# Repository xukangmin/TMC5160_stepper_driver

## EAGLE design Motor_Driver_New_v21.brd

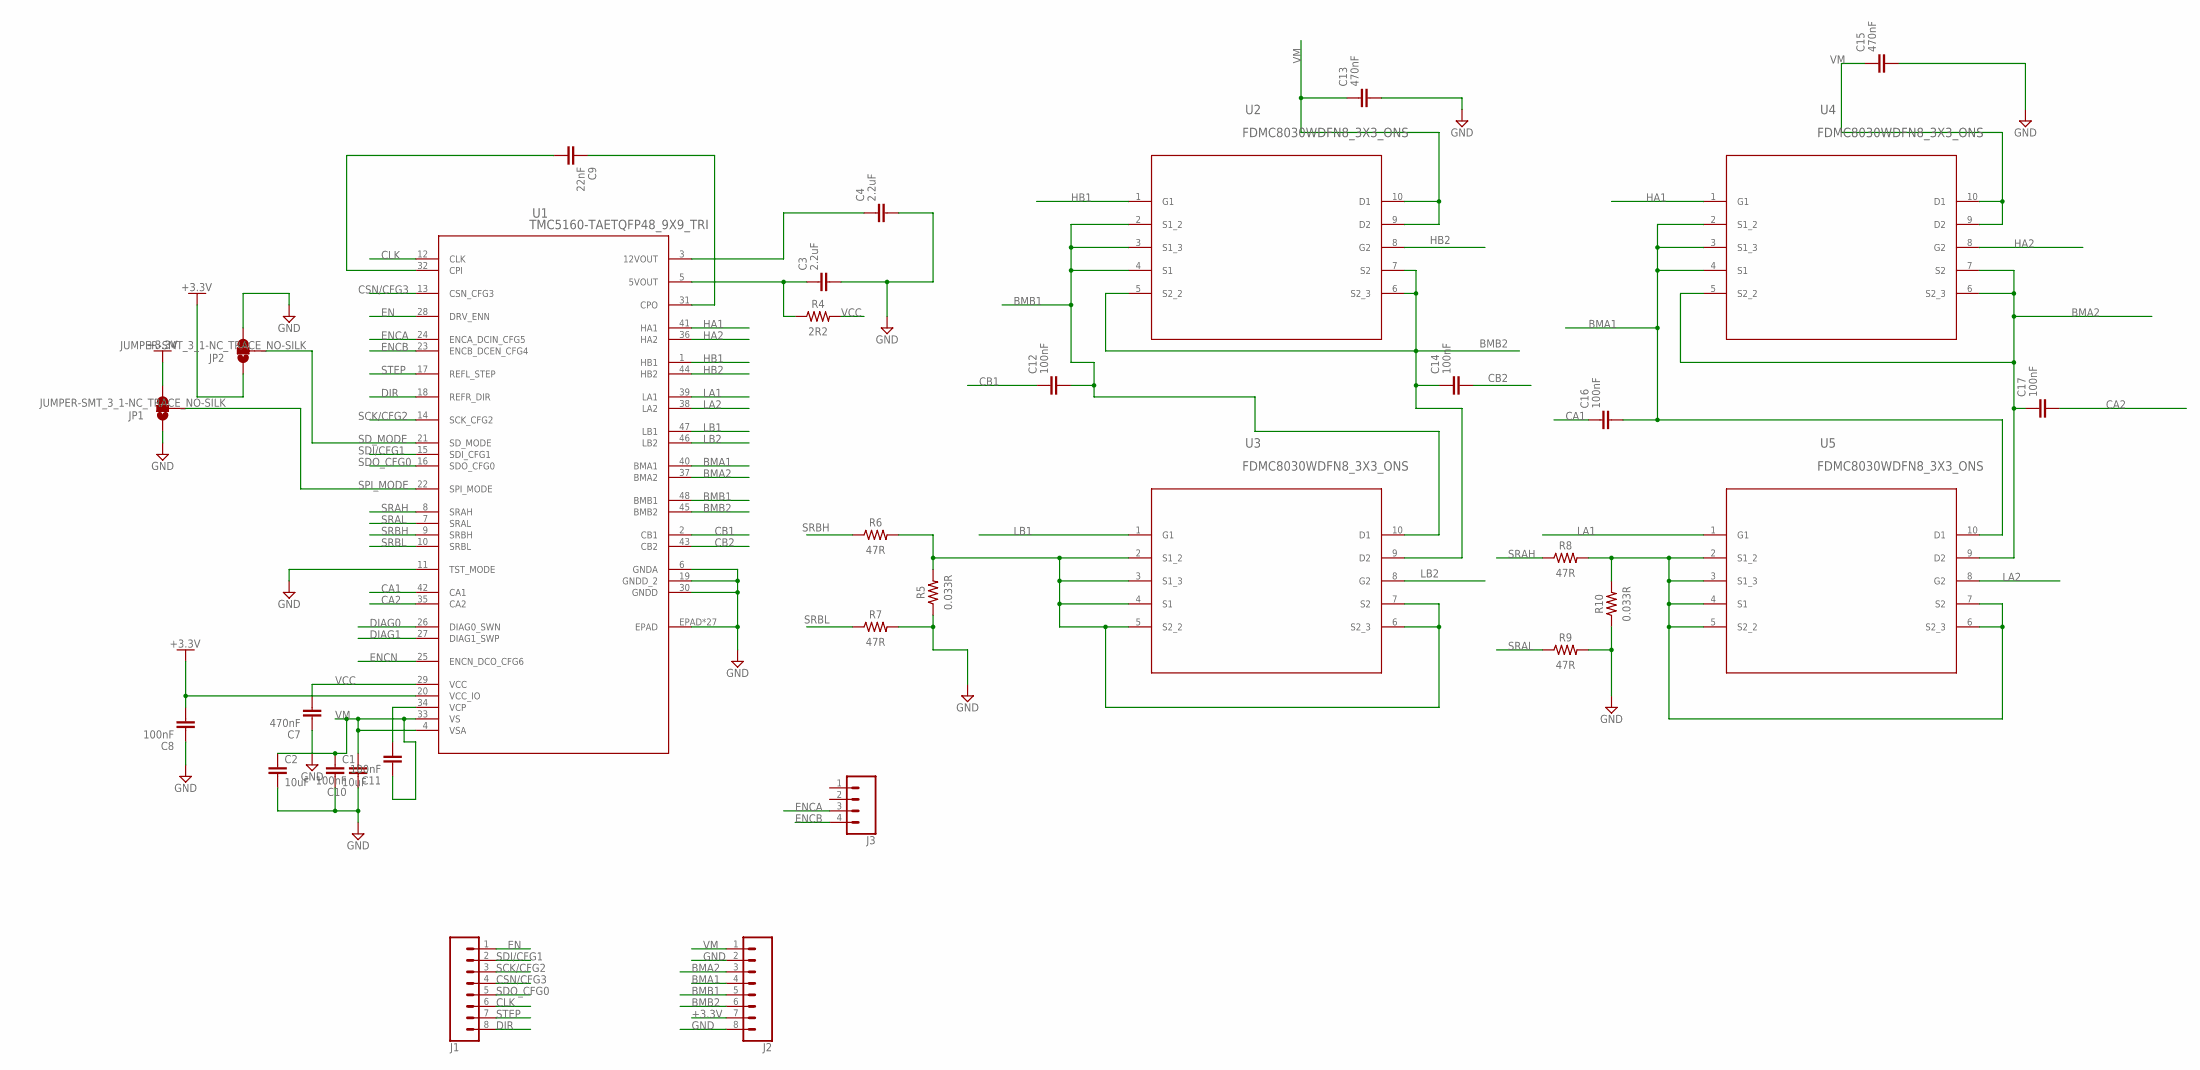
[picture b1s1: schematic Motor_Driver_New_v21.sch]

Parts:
C1, C2: 10uF; 0805
C3, C4: 2.2uF; CAPC1005X60
C7, C13, C15: 470nF; CAPC1005X60
C8, C10, C11, C12, C14, C16, C17: 100nF; CAPC1005X60
C9: 22nF; CAPC1005X60
J1, J2: CONN_08"; 1X08
J3: CONN_04PTH; 1X04
JP1, JP2: JUMPER-SMT_3_1-NC_TRACE_NO-SILK; SMT-JUMPER_3_1-NC_TRACE_NO-SILK
R4: 2R2; RESC1005X40
R5, R10: 0.033R; RESC3216X70
R6, R7, R8, R9: 47R; RESC1005X40
U1: TMC5160-TAETQFP48_9X9_TRI; ETQFP48_9X9_TRI
U2, U3, U4, U5: FDMC8030WDFN8_3X3_ONS; WDFN8_3X3_ONS

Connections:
+3.3V: C8.2, J2.7, JP1.3, JP2.1, U1.20 (VCC_IO)
BMA1: C16.2, J2.4, U1.40 (BMA1), U4.2 (S1_2), U4.3 (S1_3), U4.4 (S1), U5.10 (D1)
BMA2: C17.1, J2.3, U1.37 (BMA2), U4.5 (S2_2), U4.6 (S2_3), U4.7 (S2), U5.9 (D2)
BMB1: C12.2, J2.5, U1.48 (BMB1), U2.2 (S1_2), U2.3 (S1_3), U2.4 (S1), U3.10 (D1)
BMB2: C14.1, J2.6, U1.45 (BMB2), U2.5 (S2_2), U2.6 (S2_3), U2.7 (S2), U3.9 (D2)
CA1: C16.1, U1.42 (CA1)
CA2: C17.2, U1.35 (CA2)
CB1: C12.1, U1.2 (CB1)
CB2: C14.2, U1.43 (CB2)
CLK: J1.6, U1.12 (CLK)
CSN/CFG3: J1.4, U1.13 (CSN_CFG3)
DIAG0: U1.26 (DIAG0_SWN)
DIAG1: U1.27 (DIAG1_SWP)
DIR: J1.8, U1.18 (REFR_DIR)
EN: J1.1, U1.28 (DRV_ENN)
ENCA: J3.3, U1.24 (ENCA_DCIN_CFG5)
ENCB: J3.4, U1.23 (ENCB_DCEN_CFG4)
ENCN: U1.25 (ENCN_DCO_CFG6)
GND: C1.2, C2.2, C3.2, C4.2, C7.1, C8.1, C10.1, C13.2, C15.2, J2.2, J2.8, JP1.1, JP2.3, R5.1, R7.2, R9.2, R10.1, U1.6 (GNDA), U1.11 (TST_MODE), U1.19 (GNDD_2), U1.30 (GNDD), U1.EPAD, U1.EPAD1 (EPAD), U1.P$1 (EPAD), U1.P$2 (EPAD), U1.P$3 (EPAD), U1.P$4 (EPAD), U1.P$5 (EPAD), U1.P$6 (EPAD), U1.P$7 (EPAD), U1.P$8 (EPAD), U1.P$9 (EPAD), U1.P$10 (EPAD), U1.P$11 (EPAD), U1.P$12 (EPAD), U1.P$13 (EPAD), U1.P$14 (EPAD), U1.P$15 (EPAD), U1.P$16 (EPAD), U1.P$17 (EPAD), U1.P$18 (EPAD), U1.P$19 (EPAD), U1.P$20 (EPAD), U1.P$21 (EPAD), U1.P$22 (EPAD), U1.P$23 (EPAD), U1.P$24 (EPAD), U1.P$25 (EPAD)
HA1: U1.41 (HA1), U4.1 (G1)
HA2: U1.36 (HA2), U4.8 (G2)
HB1: U1.1 (HB1), U2.1 (G1)
HB2: U1.44 (HB2), U2.8 (G2)
LA1: U1.39 (LA1), U5.1 (G1)
LA2: U1.38 (LA2), U5.8 (G2)
LB1: U1.47 (LB1), U3.1 (G1)
LB2: U1.46 (LB2), U3.8 (G2)
unnamed: C3.1, R4.1, U1.5 (5VOUT)
unnamed: C4.1, U1.3 (12VOUT)
unnamed: C9.2, U1.32 (CPI)
unnamed: C9.1, U1.31 (CPO)
unnamed: C11.2, U1.34 (VCP)
SCK/CFG2: J1.3, U1.14 (SCK_CFG2)
SDI/CFG1: J1.2, U1.15 (SDI_CFG1)
SDO_CFG0: J1.5, U1.16 (SDO_CFG0)
SD_MODE: JP2.2, U1.21 (SD_MODE)
SPI_MODE: JP1.2, U1.22 (SPI_MODE)
SRAH: R8.1, U1.8 (SRAH)
SRAHL: R8.2, R10.2, U5.2 (S1_2), U5.3 (S1_3), U5.4 (S1), U5.5 (S2_2), U5.6 (S2_3), U5.7 (S2)
SRAL: R9.1, U1.7 (SRAL)
SRBH: R6.1, U1.9 (SRBH)
SRBHL: R5.2, R6.2, U3.2 (S1_2), U3.3 (S1_3), U3.4 (S1), U3.5 (S2_2), U3.6 (S2_3), U3.7 (S2)
SRBL: R7.1, U1.10 (SRBL)
STEP: J1.7, U1.17 (REFL_STEP)
VCC: C7.2, R4.2, U1.29 (VCC)
VM: C1.1, C2.1, C10.2, C11.1, C13.1, C15.1, J2.1, U1.4 (VSA), U1.33 (VS), U2.9 (D2), U2.10 (D1), U4.9 (D2), U4.10 (D1)

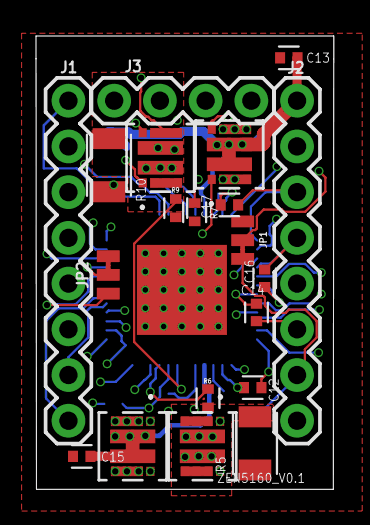
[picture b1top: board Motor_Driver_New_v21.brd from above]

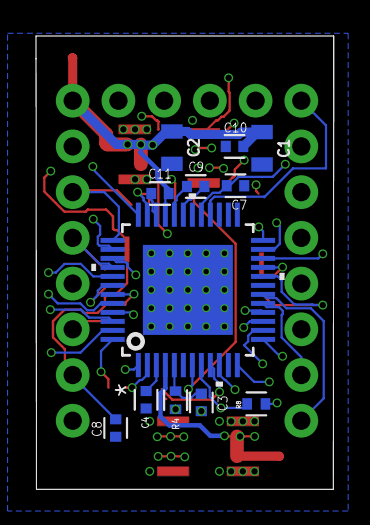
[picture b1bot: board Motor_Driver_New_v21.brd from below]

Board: 6 copper layers, 16.5 x 25.2 mm, 32 parts (12 on the bottom side), 43 nets.

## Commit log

2024-08-11 init

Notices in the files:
parts and their libraries:
SparkFun-Connectors: Licensing: Creative Commons ShareAlike 4.0 International - https://creativecommons.org/licenses/by-sa/4.0
COPYRIGHT: Copyright (C) 2023 Ultra Librarian. All rights reserved.
